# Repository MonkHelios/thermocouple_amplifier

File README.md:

# thermocouple_amplifier
Thermocouple amplifier circuit(s) for interfacing with microcontrollers. 

1. J and K type thermocouple amplifier circuit built around LTC2053 instrumentation amplifier and LT1025 cold junction compensator.
   This breakout board has analog output of X mV/degC (yet to be tested). Initially feeding it to the ADC chanel of an arduino UNO.

Project link : https://hackaday.io/project/67584-thermocouple-amplifier-for-arduino-and-other-mcu

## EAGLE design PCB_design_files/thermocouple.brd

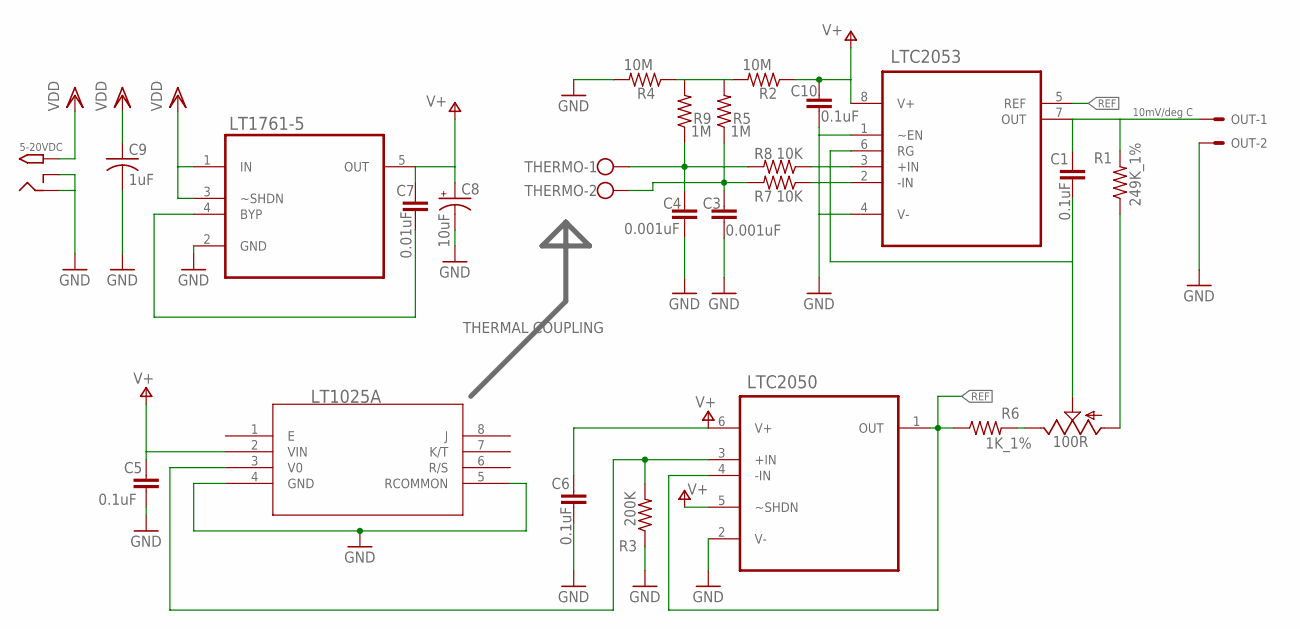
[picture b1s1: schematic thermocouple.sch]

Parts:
5-20VDC: DC_IN; PJ-102A
C1, C5, C6, C10: 0.1uF; C0805
C3, C4: 0.001uF; C0805
C7: 0.01uF; C0805
C8: 10uF; E2,5-6E
C9: 1uF; C0805
OUT: 10mV/C; 6410-02
POT: 100R; 6MM
R1: 249K_1%; R0805
R2, R4: 10M; R0805
R3: 200K; M0805
R5, R9: 1M; R0805
R6: 1K_1%; R0805
R7, R8: 10K; R0805
THERMO: W237-102
U1: LT1025A; PDIP-8_N
U2: LTC2053; SOP65P490X110-8N
U3: LTC2050; SOT95P280X100-6N
U4: LT1761-5; SOT95P280X100-5N

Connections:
GND: 5-20VDC.RING, 5-20VDC.RING_SW, C3.1, C4.2, C5.2, C6.2, C8.-, C9.2, C10.1, OUT.2, R3.1, R4.2, U1.4 (GND), U1.5 (RCOMMON), U2.1 (~EN), U2.4 (V-), U3.2 (V-), U4.2 (GND)
unnamed: C1.2, POT.S, U2.6 (RG)
unnamed: C1.1, OUT.1, R1.2, U2.7 (OUT)
unnamed: POT.A, R1.1
unnamed: R2.2, R4.1, R5.2, R9.2
unnamed: R7.1, U2.2 (-IN)
unnamed: R8.1, U2.3 (+IN)
unnamed: C3.2, R5.1, R7.2, THERMO.2
unnamed: C4.1, R8.2, R9.1, THERMO.1
unnamed: R3.2, U1.3 (V0), U3.3 (+IN)
unnamed: C7.2, U4.4 (BYP)
unnamed: POT.E, R6.2
REF: R6.1, U2.5 (REF), U3.1 (OUT), U3.4 (-IN)
V+: C5.1, C6.1, C7.1, C8.+, C10.2, R2.1, U1.2 (VIN), U2.8 (V+), U3.5 (~SHDN), U3.6 (V+), U4.5 (OUT)
VDD: 5-20VDC.TIP, C9.1, U4.1 (IN), U4.3 (~SHDN)

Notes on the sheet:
10mV/deg C
THERMAL COUPLING

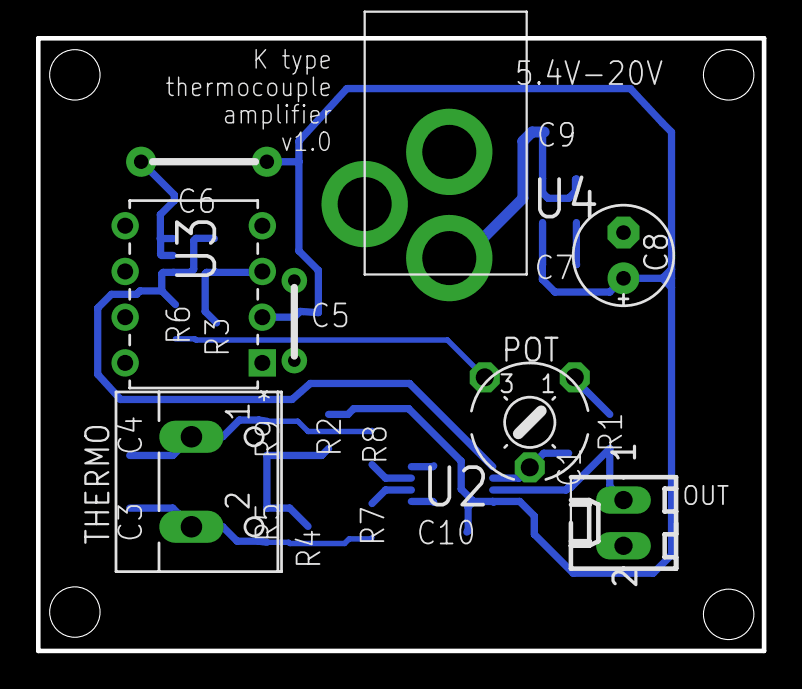
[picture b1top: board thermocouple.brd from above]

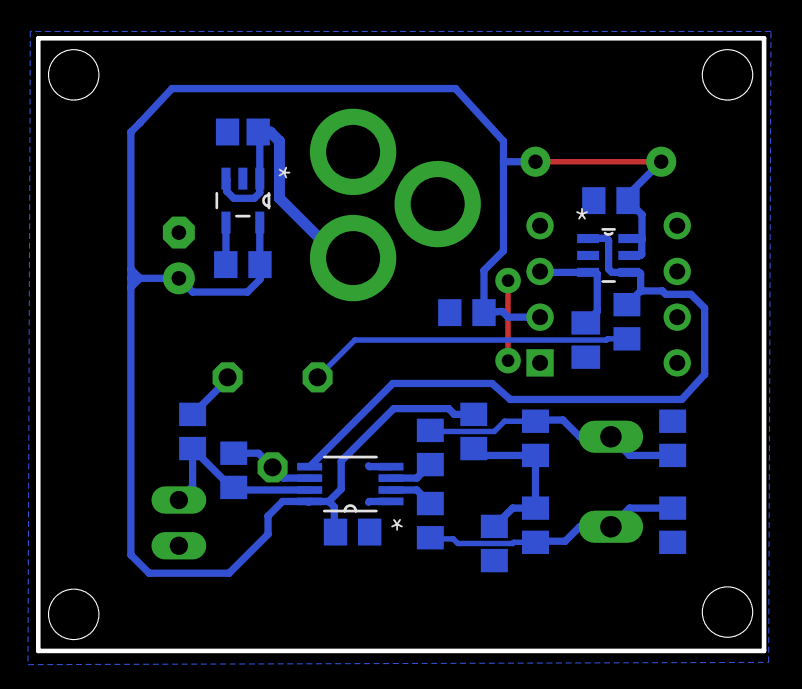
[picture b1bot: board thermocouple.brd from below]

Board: 2 copper layers, 40.3 x 34.0 mm, 26 parts (20 on the bottom side), 15 nets.

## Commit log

2018-03-03 first breakout initial description
2018-03-03 first board files
2018-03-04 datasheets of instrumentation amp and vreg
2018-03-18 updating project link
2018-03-18 new folder for pcb files
2018-03-18 board files
2018-03-18 Create sdas
2018-03-18 reference
2018-03-18 Create dads
2018-03-18 gerbers for home fabrication
2018-04-24 Create LICENSE
